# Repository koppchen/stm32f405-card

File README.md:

# STM32F405 Microcontroller Card

ARM STM32F405 microcontroller SMT to though-hole adapter card for the Touch Activated Voltage Source Model 218 Rev2.0 Buchla clone.

This repo contains the EAGLE board and schematic files along with the generated Gerber files.

## STM32F405 card

STM32F405 cards fresh from the PCB fab house

Card with the microcontroller installed

Finished card with the 218 Rev 2.0

## BOM

| Value   | QTY | Description | Mouser Part # |
|:--------|:---:|:------------|:--------------|
| STM32F405RGT6 | 1 | ARM Microcontroller - MCU ARM M4 1024 FLASH 168 Mhz 192kB SRAM | [511-STM32F405RGT6][arm-mcu] |
|  | 4 | Pin Strip Header - 16 Pin (Male) | [517-929700-01-16][pin-header] |
|  | 4 | Pin Strip Header - 16 Pin Socket (Female) | [517-929974-01-16-RK][pin-socket]

[arm-mcu]: https://www.mouser.com/ProductDetail/511-STM32F405RGT6
[pin-header]: https://www.mouser.com/ProductDetail/517-929700-01-16
[pin-socket]: https://www.mouser.com/ProductDetail/517-929974-01-16-RK

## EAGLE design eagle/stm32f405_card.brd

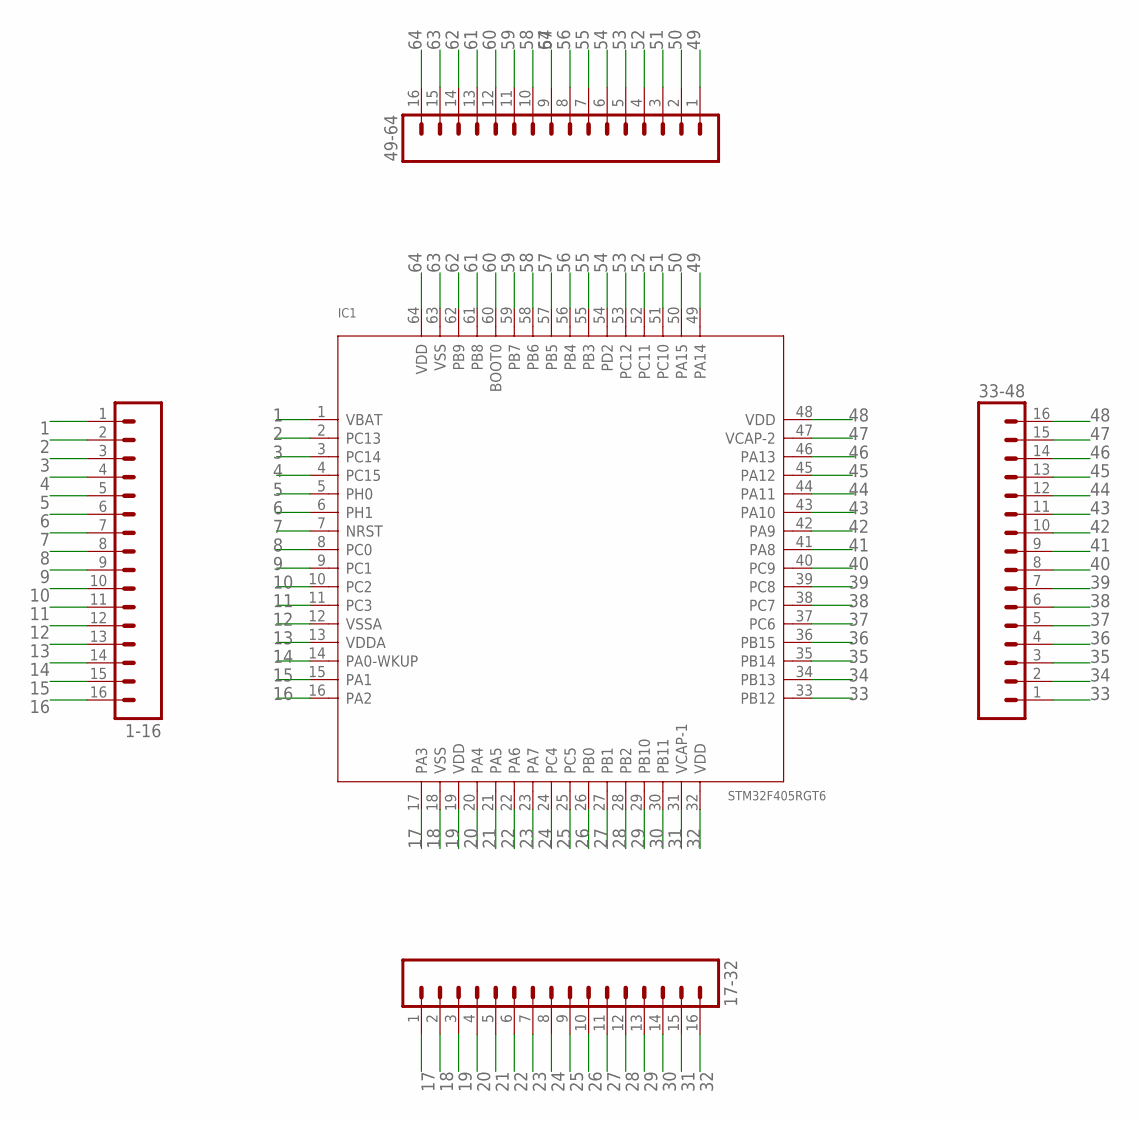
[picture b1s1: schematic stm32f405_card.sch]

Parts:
1-16: M16PTH_SQ_BOTTOM; 1X16_SQ_BOTTOM
17-32, 33-48, 49-64: M16PTH_BOTTOM; 1X16_BOTTOM
IC1: STM32F405RGT6; LQFP64-0.5-10X10MM

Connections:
1: 1-16.1, IC1.1 (VBAT)
2: 1-16.2, IC1.2 (PC13)
3: 1-16.3, IC1.3 (PC14)
4: 1-16.4, IC1.4 (PC15)
5: 1-16.5, IC1.5 (PH0)
6: 1-16.6, IC1.6 (PH1)
7: 1-16.7, IC1.7 (NRST)
8: 1-16.8, IC1.8 (PC0)
9: 1-16.9, IC1.9 (PC1)
10: 1-16.10, IC1.10 (PC2)
11: 1-16.11, IC1.11 (PC3)
12: 1-16.12, IC1.12 (VSSA)
13: 1-16.13, IC1.13 (VDDA)
14: 1-16.14, IC1.14 (PA0-WKUP)
15: 1-16.15, IC1.15 (PA1)
16: 1-16.16, IC1.16 (PA2)
17: 17-32.1, IC1.17 (PA3)
18: 17-32.2, IC1.18 (VSS)
19: 17-32.3, IC1.19 (VDD)
20: 17-32.4, IC1.20 (PA4)
21: 17-32.5, IC1.21 (PA5)
22: 17-32.6, IC1.22 (PA6)
23: 17-32.7, IC1.23 (PA7)
24: 17-32.8, IC1.24 (PC4)
25: 17-32.9, IC1.25 (PC5)
26: 17-32.10, IC1.26 (PB0)
27: 17-32.11, IC1.27 (PB1)
28: 17-32.12, IC1.28 (PB2)
29: 17-32.13, IC1.29 (PB10)
30: 17-32.14, IC1.30 (PB11)
31: 17-32.15, IC1.31 (VCAP-1)
32: 17-32.16, IC1.32 (VDD)
33: 33-48.1, IC1.33 (PB12)
34: 33-48.2, IC1.34 (PB13)
35: 33-48.3, IC1.35 (PB14)
36: 33-48.4, IC1.36 (PB15)
37: 33-48.5, IC1.37 (PC6)
38: 33-48.6, IC1.38 (PC7)
39: 33-48.7, IC1.39 (PC8)
40: 33-48.8, IC1.40 (PC9)
41: 33-48.9, IC1.41 (PA8)
42: 33-48.10, IC1.42 (PA9)
43: 33-48.11, IC1.43 (PA10)
44: 33-48.12, IC1.44 (PA11)
45: 33-48.13, IC1.45 (PA12)
46: 33-48.14, IC1.46 (PA13)
47: 33-48.15, IC1.47 (VCAP-2)
48: 33-48.16, IC1.48 (VDD)
49: 49-64.1, IC1.49 (PA14)
50: 49-64.2, IC1.50 (PA15)
51: 49-64.3, IC1.51 (PC10)
52: 49-64.4, IC1.52 (PC11)
53: 49-64.5, IC1.53 (PC12)
54: 49-64.6, IC1.54 (PD2)
55: 49-64.7, IC1.55 (PB3)
56: 49-64.8, IC1.56 (PB4)
57: 49-64.9, IC1.57 (PB5)
58: 49-64.10, IC1.58 (PB6)
59: 49-64.11, IC1.59 (PB7)
60: 49-64.12, IC1.60 (BOOT0)
61: 49-64.13, IC1.61 (PB8)
62: 49-64.14, IC1.62 (PB9)
63: 49-64.15, IC1.63 (VSS)
64: 49-64.16, IC1.64 (VDD)

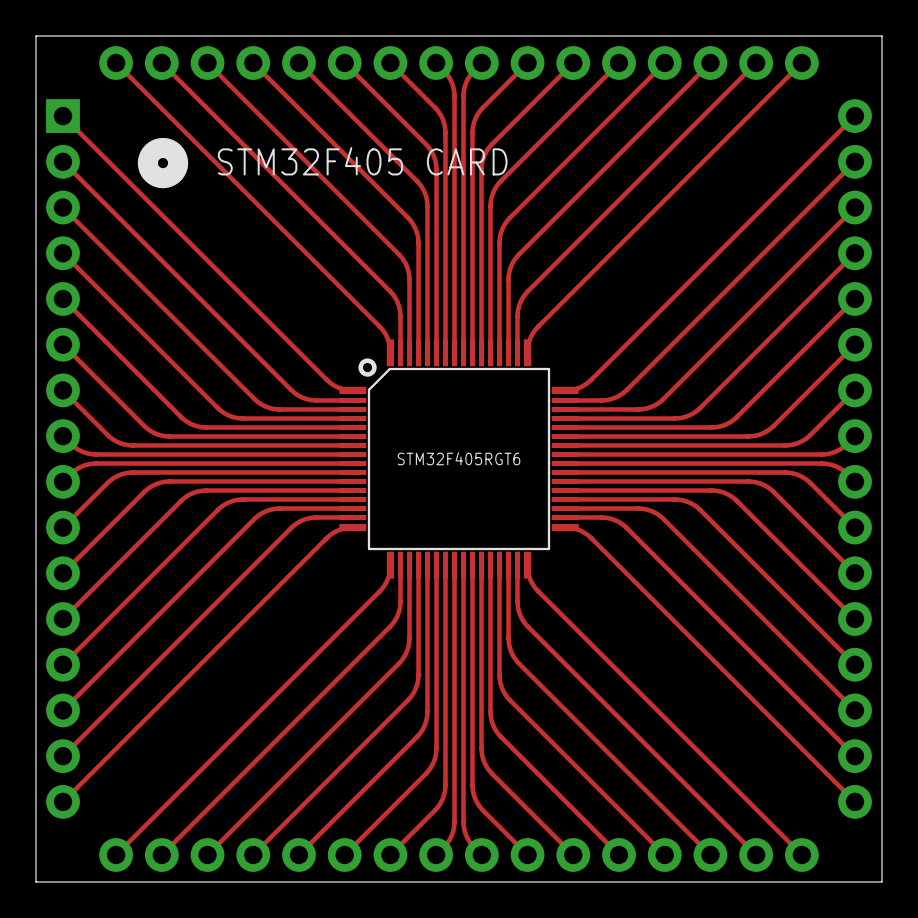
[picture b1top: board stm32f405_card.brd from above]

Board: 2 copper layers, 47.0 x 47.0 mm, 5 parts (0 on the bottom side), 64 nets.

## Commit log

2018-04-17 Add EAGLE files along with documentation
2018-04-17 Small section name change
2018-04-17 Add 16 pin socket headers to BOM and minor BOM changes
